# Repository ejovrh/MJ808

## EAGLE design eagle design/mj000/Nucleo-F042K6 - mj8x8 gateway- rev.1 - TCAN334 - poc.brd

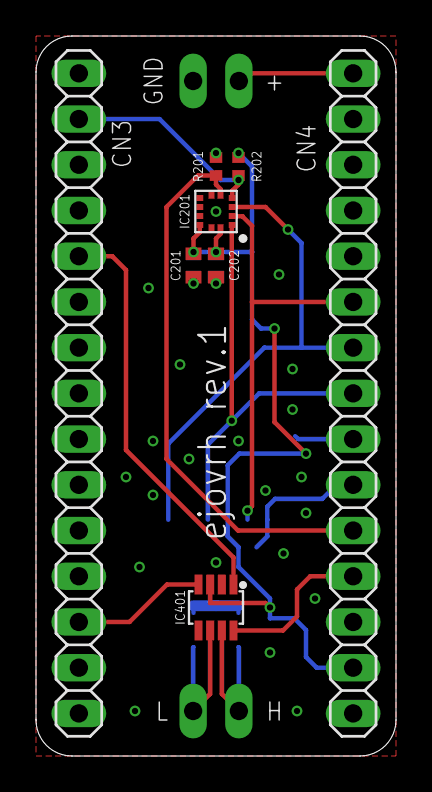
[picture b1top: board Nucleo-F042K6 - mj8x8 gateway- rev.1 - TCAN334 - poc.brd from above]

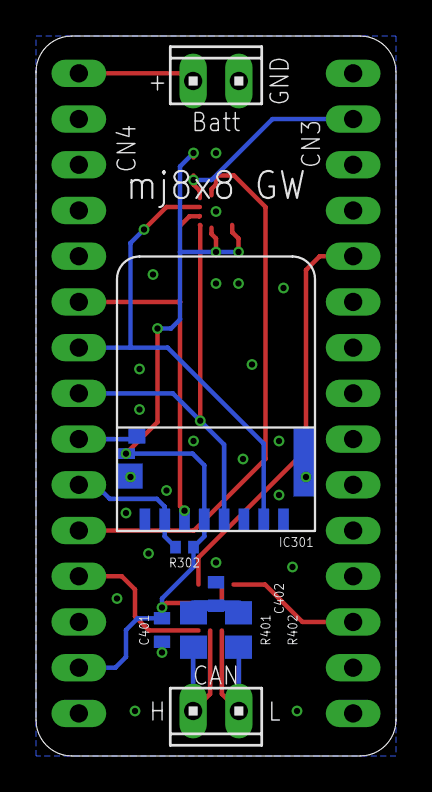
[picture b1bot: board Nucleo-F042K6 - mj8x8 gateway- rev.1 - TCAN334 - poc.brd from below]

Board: 2 copper layers, 20.0 x 40.0 mm, 16 parts (8 on the bottom side), 17 nets.

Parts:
C201, C202: 0.1u; C0402
C401: 0.1uF / 10V; C0402
C402: 47nF / 10V; C0402
IC201: ADXL367; LGA
IC301: 47309-2651; MICRO_SD_CONNECTOR
IC401: TCAN334; SOT23-8
J1, J2: Batt; 10X02MTA
JP1: CN3; 1X15
JP2: CN4; 1X15
R201, R202, R302: 10k; R0402
R401, R402: 60; R0805

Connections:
3V3: C201.1, C202.1, C401.1, IC201.10, IC201.12, IC301.G3, IC301.PIN4, IC401.P$3, JP2.14, R202.2, R302.2
!STBY!: IC401.P$8, JP2.12
ADXL367_CS: IC201.4, JP1.2, R202.1
ADXL367_INT1: IC201.5, JP2.11, R201.2
CANH: IC401.P$7, J2.1, R401.2
CANL: IC401.P$6, J2.2, R402.1
CAN_INFRA:SPLIT: C402.1, R401.1, R402.2
CLK: IC201.1, IC301.PIN5, JP2.8
GND: C201.2, C202.2, C401.2, C402.2, IC201.7, IC201.11, IC301.G1, IC301.G2, IC301.PIN6, IC401.P$2, J1.1, JP1.4, JP2.2, R201.1
MISO: IC201.3, IC301.PIN7, JP2.7
MOSI: IC201.2, IC301.PIN3, JP2.6
RST: JP1.3, JP2.3
RXCAN: IC401.P$4, JP1.13
SD_CS: IC301.PIN2, JP2.10, R302.1
SD_DET: IC301.G4, JP2.9
TXCAN: IC401.P$1, JP1.5
VIN: J1.2, JP2.1

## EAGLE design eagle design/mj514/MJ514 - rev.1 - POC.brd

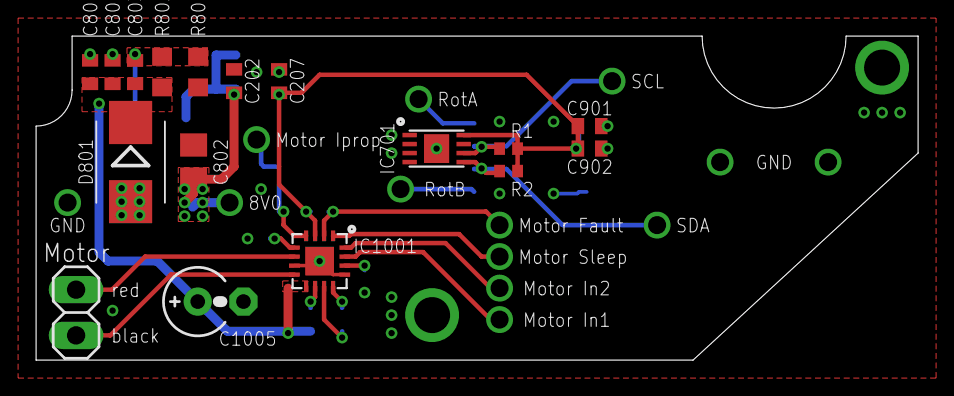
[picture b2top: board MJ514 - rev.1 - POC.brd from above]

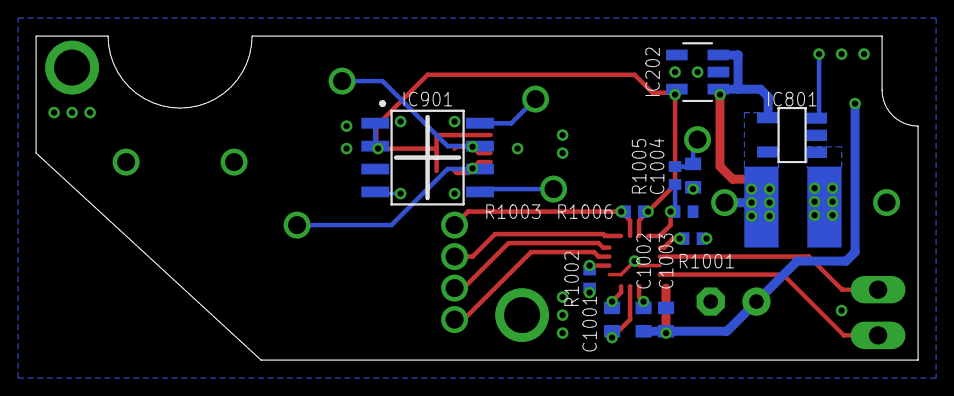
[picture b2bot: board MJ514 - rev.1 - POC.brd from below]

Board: 2 copper layers, 49.0 x 18.0 mm, 30 parts (13 on the bottom side), 18 nets.

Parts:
C202, C207: 1uF / 10V; C0402
C801, C804: 10u / 50V; C0402
C802: 4.7u / 50V; C0805
C803: 68p / 50V; C0402
C901: 1u / 16V; C0402
C902: 10u / 16V; C0402
C1001: 22n / 50V; C0402
C1002, C1004: 0.1u / 50V; C0402
C1003: 0.1u / 16V; C0402
C1005: 100u / 25V; E2,5RE
D801: MBRM120LT3G; SMB
IC202: LDK320AM33R; SOT-23-5L
IC701: MB85RC16PN-G-AMERE1; SON-8
IC801: LT1935ES5#TRMPBF; TSOT-23-5
IC901: AS5601-ASOM; SOIC8
IC1001: DRV8876RGTR; VQFN16
JP3: 1X02
L801: CDRH4D18NP-4R7NC; 5050
R1, R2: 4k7; R0402
R801: 10k; R0603
R802: 85.6k; R0603
R1001, R1002: foo; R0402
R1003: 10k; R0402
R1005: 2.2k; R0402
R1006: 1k; R0402

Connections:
3V3: C207.2, C901.1, C902.1, IC202.OUT, IC701.P$8, IC901.P$1, IC901.P$2, IC1001.P$3, R1.2, R2.2, R1003.2
12V0: C801.1, C803.1, C804.1, C1002.2, C1003.2, C1005.+, D801.C, IC1001.P$9, R802.2
12V0:FB: C803.2, IC801.FB, R801.2, R802.1
12V0:SW: D801.A, IC801.SW, L801.P$2
BAT+: C202.1, C802.2, IC202.EN, IC202.IN, IC801.!SHDN!, IC801.VIN, L801.P$1
GND: C202.2, C207.1, C801.2, C802.1, C804.2, C901.2, C902.2, C1003.1, C1004.2, C1005.-, IC202.GND, IC701.P$1, IC701.P$2, IC701.P$3, IC701.P$4, IC701.P$9, IC801.GND, IC901.P$4, IC1001.P$7, IC1001.P$13, IC1001.P$17, R801.1, R1001.1, R1002.1, R1006.1
I2C_SCL: IC701.P$6, IC901.P$7, R1.1
I2C_SDA: IC701.P$5, IC901.P$6, R2.1
MC:CPH: C1001.1, IC1001.P$11
MC:CPL: C1001.2, IC1001.P$12
MC:IMODE: IC1001.P$5, R1001.2
MC:IPROPI: IC1001.P$4, R1005.2, R1006.2
MC:PMODE: IC1001.P$14, R1002.2
MC:VCP: C1002.1, IC1001.P$10
MOTOR+: IC1001.P$6, JP3.1
MOTOR-: IC1001.P$8, JP3.2
MOTOR_FLT: IC1001.P$2, R1003.1
MOTOR_IPROP: C1004.1, R1005.1

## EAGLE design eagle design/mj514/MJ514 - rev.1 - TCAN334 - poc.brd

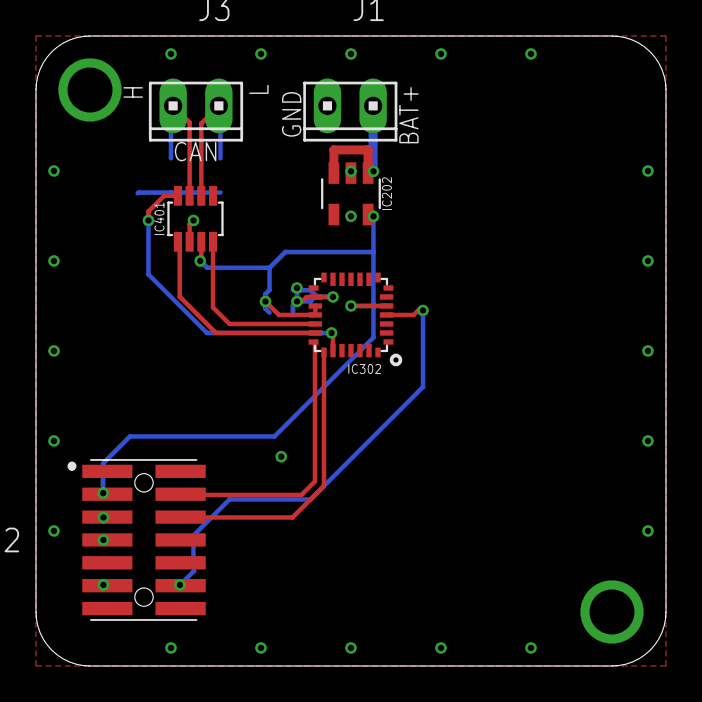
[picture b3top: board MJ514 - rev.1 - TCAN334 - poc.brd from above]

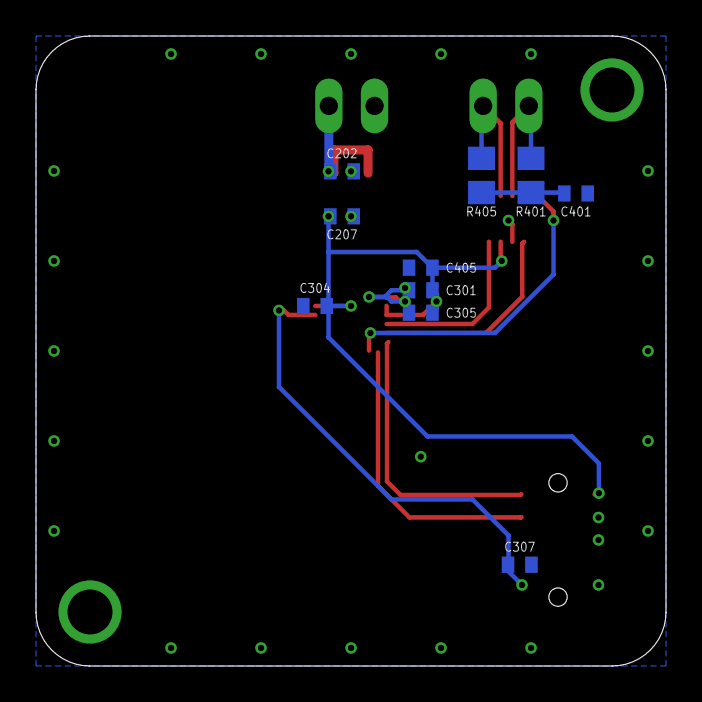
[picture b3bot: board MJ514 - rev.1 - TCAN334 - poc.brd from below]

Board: 2 copper layers, 35.0 x 35.0 mm, 16 parts (10 on the bottom side), 12 nets.

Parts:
C202, C207, C304: 1uF / 10V; C0402
C301, C305, C307, C405: 0.1uF / 10V; C0402
C401: 47nF / 10V; C0402
IC202: LDK320AM33R; SOT-23-5L
IC302: STM32F042G6U6; UFQFPN-28
IC401: TCAN334; SOT23-8
J1: Power Supply; 10X02MTA
J2: FTSH-107-01-L-DV-K-A; FTSH10701LDVKA
J3: CAN; 10X02MTA
R401, R405: 60; R0805

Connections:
3V3: C207.2, C301.2, C304.2, C305.2, C405.1, IC202.OUT, IC302.5_VDDA, IC302.17_VDD, IC302.18_VDDIO2, IC401.P$3, J2.3
!STBY!: IC302.23_PA15, IC401.P$8
BAT+: C202.1, IC202.EN, IC202.IN, J1.2
CAN_H: IC401.P$7, J3.1, R401.2
CAN_INFRA:SPLIT: C401.1, R401.1, R405.2
CAN_L: IC401.P$6, J3.2, R405.1
CAN_RX: IC302.19_PA9-[PA11], IC401.P$4
CAN_TX: IC302.20_PA10-[PA12], IC401.P$1
GND: C202.2, C207.1, C301.1, C304.1, C305.1, C307.1, C401.2, C405.2, IC202.GND, IC302.16_VSS, IC401.P$2, J1.1, J2.5, J2.7, J2.11
SYS_NRST: C307.2, IC302.4_NRST, J2.12
SYS_SWCLK: IC302.22_PA14, J2.6
SYS_SWDIO: IC302.21_PA13, J2.4

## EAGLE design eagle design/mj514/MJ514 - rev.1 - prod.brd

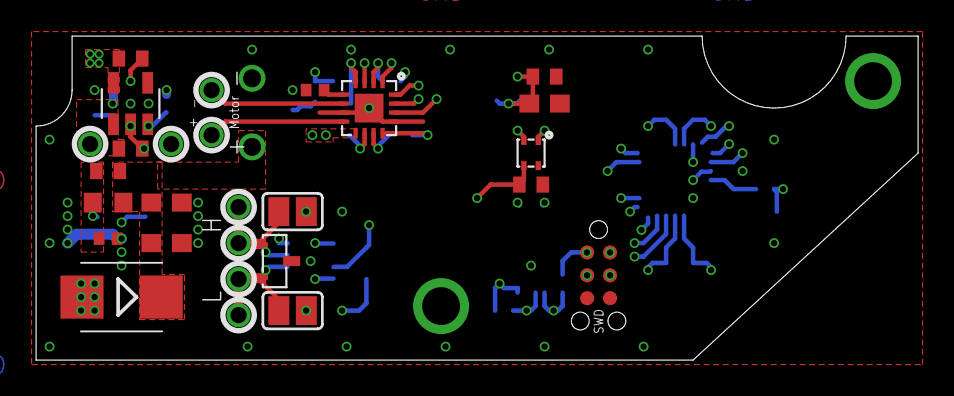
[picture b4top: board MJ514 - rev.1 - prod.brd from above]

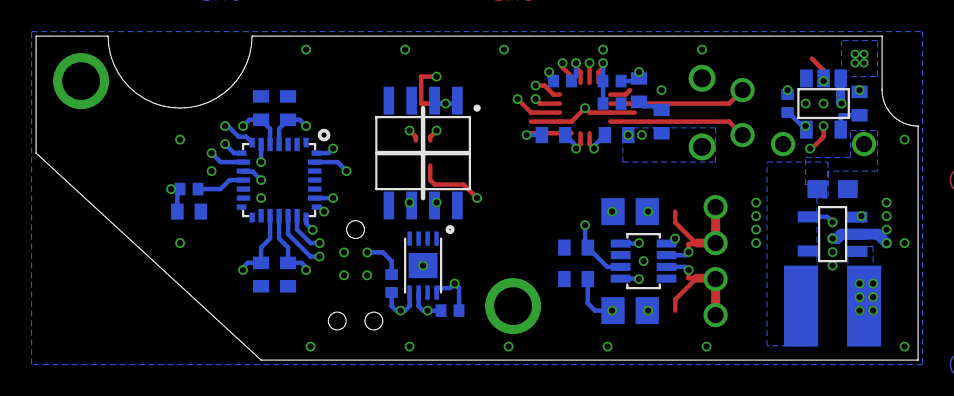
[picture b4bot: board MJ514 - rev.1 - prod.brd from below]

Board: 6 copper layers, 49.0 x 18.0 mm, 57 parts (29 on the bottom side), 35 nets.

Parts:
C201, C203, C204, C304, C701: 1uF / 10V; C0402
C301, C305, C307, C405, C501, C902, C903, C904: 0.1uF / 100V; C0402
C402: 47nF / 10V; C0402
C702, C801, C804: 10uF / 35V; C0603
C802: 4.7uF / 50V; C0603
C803: 68pF / 50V; C0402
C805: 0.22uF / 50V; C0402
C901: 22nF / 50V; C0402
C906: 100uF / 25V; TH
D801: MBRM120LT3G; SMB
IC201: LDK320AM33R; SOT-23-5L
IC203: R3119N058A-TR-FE; SOT23-5
IC302: STM32F042G6U6; UFQFPN-28
IC401: TCAN334; SOT23-8
IC402: SZNUP2105LT1G; SOT-23-3
IC501: SHT40-AD1F-R2; SMD
IC601: MB85RC16PN-G-AMERE1; SON-8
IC701: AS5601-ASOM; SOIC8
IC801: LT1935ES5#TRMPBF; TSOT-23-5
IC901: DRV8876RGTR; VQFN16
L801: CDRH4D18NP-4R7NC; 5050
R1, R2: 4k7; R0402
R201: 100k; R0402
R402, R403: 60R, 0.5W; R0805
R801, R803, R903: 10k; R0402
R802: 85.6k; R0603
R901: foo; R0402
R905: 2.2k; R0402
R906: 1k; R0402
SJ401: CAN H term.; SJ
SJ402: CAN L term.; SJ
SWD1: TC2030-NL
TP1: LiIon + Terminal; TH-0.9
TP2: LiIon - Terminal; TH-0.9
TP3, TP4: CAN high; TH-0.9
TP5, TP6: CAN low; TH-0.9
TP7: motor +; TH-0.9
TP8: motor -; TH-0.9

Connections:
3V3: C203.2, C301.2, C304.2, C305.2, C405.1, C501.1, C701.1, C702.1, IC201.OUT, IC302.5_VDDA, IC302.17_VDD, IC302.18_VDDIO2, IC401.P$3, IC501.VDD, IC601.P$8, IC701.P$1, IC701.P$2, IC901.P$3, IC901.P$14, R1.2, R2.2, R903.2, SWD1.1_TVCC
12V: C801.1, C803.1, C804.1, C902.2, C903.2, C906.POS, D801.C, IC901.P$9, R802.2
12V0:!SHDN!_IN: C805.1, IC801.!SHDN!, R803.1
12V0:FB: C803.2, IC801.FB, R801.2, R802.1
12V0:SW: D801.A, IC801.SW, L801.P$2
12V0_!SHDN!: IC302.11_PA5, R803.2
!STBY!: IC302.23_PA15, IC401.P$8
BAT+: C201.1, C802.2, IC201.IN, IC203.1_VDD, IC801.VIN, L801.P$1, R201.1, TP1.P$1
CAN_H: IC401.P$7, IC402.1, SJ401.1, TP3.P$1, TP4.P$1
CAN_INFRA:H: R403.2, SJ401.2
CAN_INFRA:L: R402.1, SJ402.2
CAN_INFRA:SPLIT: C402.1, R402.2, R403.1
CAN_L: IC401.P$6, IC402.2, SJ402.1, TP5.P$1, TP6.P$1
CAN_RX: IC302.19_PA9-[PA11], IC401.P$4
CAN_TX: IC302.20_PA10-[PA12], IC401.P$1
GND: C201.2, C203.1, C204.2, C301.1, C304.1, C305.1, C307.1, C402.2, C405.2, C501.2, C701.2, C702.2, C801.2, C802.1, C804.2, C805.2, C903.1, C904.2, C906.NEG, IC201.GND, IC203.2_GND, IC203.3_GND, IC302.16_VSS, IC401.P$2, IC402.3, IC501.VSS, IC601.P$1, IC601.P$2, IC601.P$3, IC601.P$4, IC601.P$9, IC701.P$4, IC801.GND, IC901.P$7, IC901.P$13, IC901.P$17, R801.1, R901.1, R906.1, SWD1.5_GND, TP2.P$1
I2C_SCL: IC302.27_PB6, IC501.SCL, IC601.P$6, IC701.P$7, R1.1
I2C_SDA: IC302.28_PB7, IC501.SDA, IC601.P$5, IC701.P$6, R2.1
MC:CPH: C901.1, IC901.P$11
MC:CPL: C901.2, IC901.P$12
MC:IMODE: IC901.P$5, R901.2
MC:IPROPI: IC901.P$4, R905.2, R906.2
MC:VCP: C902.1, IC901.P$10
MOTOR+: IC901.P$6, TP7.P$1
MOTOR-: IC901.P$8, TP8.P$1
MOTOR_FLT: IC302.8_PA2, IC901.P$2, R903.1
MOTOR_IN1: IC302.6_PA0, IC901.P$15
MOTOR_IN2: IC302.7_PA1, IC901.P$16
MOTOR_IPROP: C904.1, IC302.10_PA4, R905.1
MOTOR_SLP: IC302.9_PA3, IC901.P$1
POWER_3V3:CD: C204.1, IC203.5_CD
POWER_3V3:EN: IC201.EN, IC203.4_DOUT, R201.2
SYS_NRST: C307.2, IC302.4_NRST, SWD1.3_T_NRST
SYS_SWCLK: IC302.22_PA14, SWD1.4_T_SWCLK
SYS_SWDIO: IC302.21_PA13, SWD1.2_T_SWDIO

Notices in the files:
parts and their libraries:
tag-connect: ©2009 ROFA.cz - modified and updated by Robert Darlington ‹rdarlington@gmail.com›
